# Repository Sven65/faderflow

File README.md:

# faderflow

> Fluid control over your desktop audio

A hardware audio mixer with motorized faders, full-color displays, and automatic application detection.

## Features

- 🎛️ 5 motorized faders with position sensing
- 🖥️ 5x 1.54" color TFT displays (240x240)
- 🔄 Bidirectional sync between hardware and Windows
- 🎯 Automatic app detection
- 📄 Multi-page navigation
- 💾 SD card icon storage

## Hardware

- Arduino Mega 2560
- 5x Behringer X32 Motorized Faders
- 3x DRV8833 Motor Driver Boards
- 6x ST7789 TFT Displays (1.54", 240x240)
- 6x EC11 Rotary Encoders
- SD Card Module
- USB-C PD Power (5V 3A)

## Software Stack

- **Desktop:** Rust + iced
- **Firmware:** Arduino C++
- **Platform:** Windows (Linux planned)

## Quick Start
```bash
# Clone repo
git clone https://github.com/Sven65/faderflow.git

# Build desktop app
cd desktop
cargo build --release

# Flash firmware
# Open firmware/faderflow/faderflow.ino in Arduino IDE
```

## Status

🚧 **Work in Progress** - Hardware picked out, software in development

## License

MIT License - see [LICENSE](LICENSE)

## Acknowledgments

Inspired by [deej](https://github.com/omriharel/deej)

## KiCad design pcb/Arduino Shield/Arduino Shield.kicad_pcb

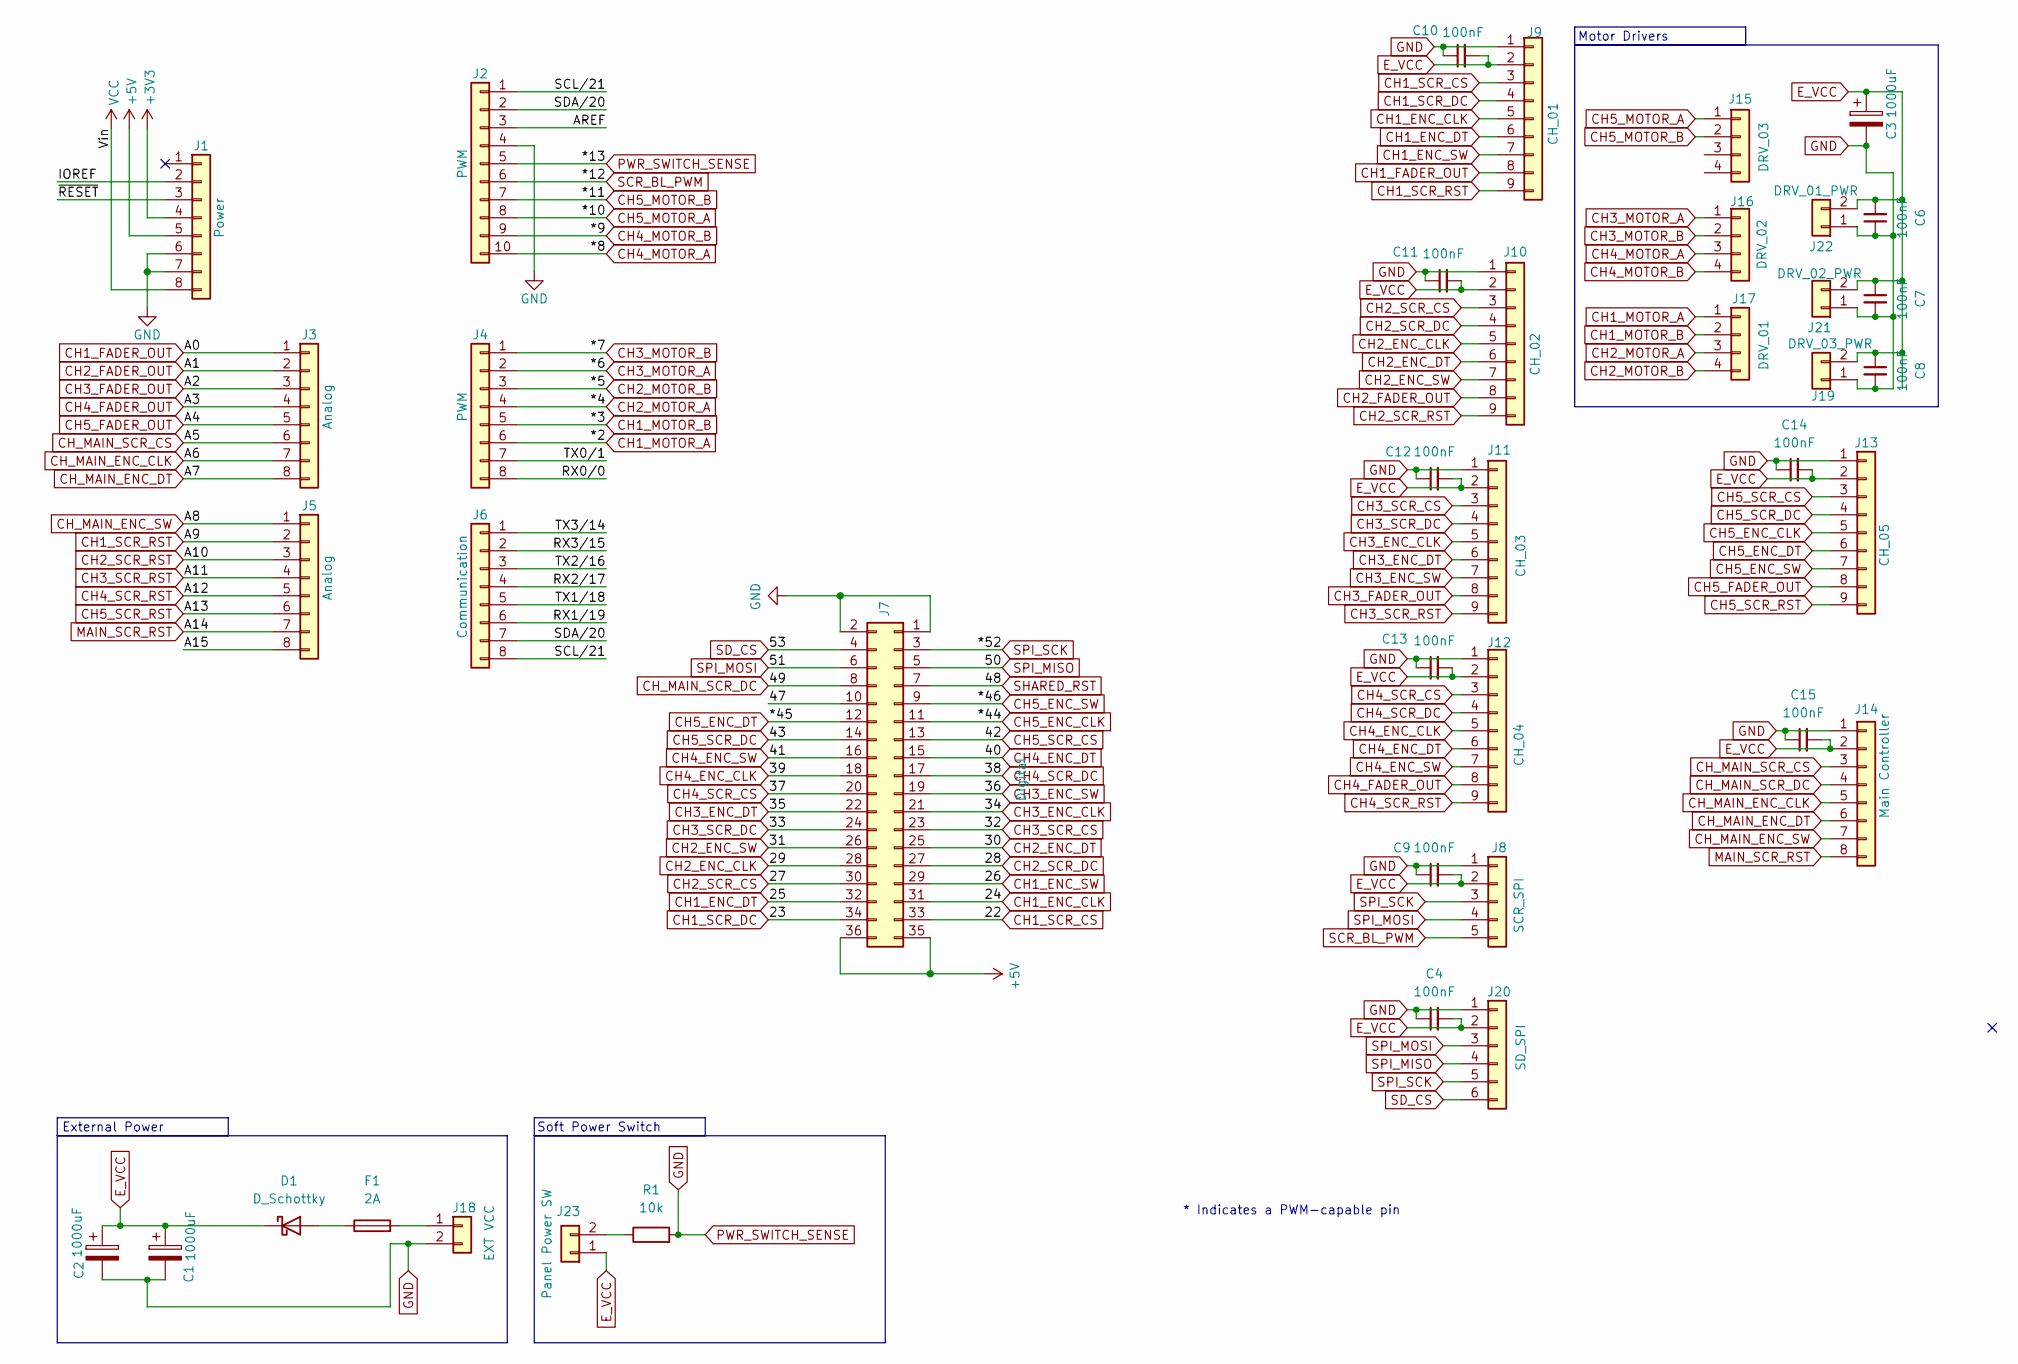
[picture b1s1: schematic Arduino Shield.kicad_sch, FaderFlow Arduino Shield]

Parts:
C1, C2, C3: 1000uF; CP_Radial_D8.0mm_P3.50mm
C4, C6, C7, C8, C9, C10, C11, C12, C13, C14, C15: 100nF; C_Disc_D5.0mm_W2.5mm_P5.00mm
D1: D_Schottky; D_DO-201AD_P15.24mm_Horizontal
F1: 2A; Fuseholder_Clip-5x20mm_Eaton_1A5601-01_Inline_P20.80x6.76mm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
J1: Power; PinSocket_1x08_P2.54mm_Vertical
J2: PWM; PinSocket_1x10_P2.54mm_Vertical
J3, J5: Analog; PinSocket_1x08_P2.54mm_Vertical
J4: PWM; PinSocket_1x08_P2.54mm_Vertical
J6: Communication; PinSocket_1x08_P2.54mm_Vertical
J7: Digital; PinSocket_2x18_P2.54mm_Vertical
J8: SCR_SPI; PinSocket_1x05_P2.00mm_Vertical
J9: CH_01; PinSocket_1x09_P2.00mm_Vertical
J10: CH_02; PinSocket_1x09_P2.00mm_Vertical
J11: CH_03; PinSocket_1x09_P2.00mm_Vertical
J12: CH_04; PinSocket_1x09_P2.00mm_Vertical
J13: CH_05; PinSocket_1x09_P2.00mm_Vertical
J14: Main Controller; PinSocket_1x08_P2.00mm_Vertical
J15: DRV_03; PinSocket_1x04_P2.00mm_Vertical
J16: DRV_02; PinSocket_1x04_P2.00mm_Vertical
J17: DRV_01; PinSocket_1x04_P2.00mm_Vertical
J18: EXT VCC; PinSocket_1x02_P2.00mm_Vertical
J19: DRV_03_PWR; PinSocket_1x02_P2.00mm_Vertical
J20: SD_SPI; PinSocket_1x06_P2.00mm_Vertical
J21: DRV_02_PWR; PinSocket_1x02_P2.00mm_Vertical
J22: DRV_01_PWR; PinSocket_1x02_P2.00mm_Vertical
J23: Panel Power SW; PinSocket_1x02_P2.00mm_Vertical
R1: 10k; R_Axial_DIN0207_L6.3mm_D2.5mm_P10.16mm_Horizontal

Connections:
+3V3: J1.4
+5V: J1.5, J7.35, J7.36
/47: J7.10
/A15: J5.8
/AREF: J2.3
/IOREF: J1.2
/RX0/0: J4.8
/RX1/19: J6.6
/RX2/17: J6.4
/RX3/15: J6.2
/SCL/21: J2.1, J6.8
/SDA/20: J2.2, J6.7
/TX0/1: J4.7
/TX1/18: J6.5
/TX2/16: J6.3
/TX3/14: J6.1
/~RESET: J1.3
CH1_ENC_CLK: J7.31, J9.5
CH1_ENC_DT: J7.32, J9.6
CH1_ENC_SW: J7.29, J9.7
CH1_FADER_OUT: J3.1, J9.8
CH1_MOTOR_A: J4.6, J17.1
CH1_MOTOR_B: J4.5, J17.2
CH1_SCR_CS: J7.33, J9.3
CH1_SCR_DC: J7.34, J9.4
CH1_SCR_RST: J5.2, J9.9
CH2_ENC_CLK: J7.28, J10.5
CH2_ENC_DT: J7.25, J10.6
CH2_ENC_SW: J7.26, J10.7
CH2_FADER_OUT: J3.2, J10.8
CH2_MOTOR_A: J4.4, J17.3
CH2_MOTOR_B: J4.3, J17.4
CH2_SCR_CS: J7.30, J10.3
CH2_SCR_DC: J7.27, J10.4
CH2_SCR_RST: J5.3, J10.9
CH3_ENC_CLK: J7.21, J11.5
CH3_ENC_DT: J7.22, J11.6
CH3_ENC_SW: J7.19, J11.7
CH3_FADER_OUT: J3.3, J11.8
CH3_MOTOR_A: J4.2, J16.1
CH3_MOTOR_B: J4.1, J16.2
CH3_SCR_CS: J7.23, J11.3
CH3_SCR_DC: J7.24, J11.4
CH3_SCR_RST: J5.4, J11.9
CH4_ENC_CLK: J7.18, J12.5
CH4_ENC_DT: J7.15, J12.6
CH4_ENC_SW: J7.16, J12.7
CH4_FADER_OUT: J3.4, J12.8
CH4_MOTOR_A: J2.10, J16.3
CH4_MOTOR_B: J2.9, J16.4
CH4_SCR_CS: J7.20, J12.3
CH4_SCR_DC: J7.17, J12.4
CH4_SCR_RST: J5.5, J12.9
CH5_ENC_CLK: J7.11, J13.5
CH5_ENC_DT: J7.12, J13.6
CH5_ENC_SW: J7.9, J13.7
CH5_FADER_OUT: J3.5, J13.8
CH5_MOTOR_A: J2.8, J15.1
CH5_MOTOR_B: J2.7, J15.2
CH5_SCR_CS: J7.13, J13.3
CH5_SCR_DC: J7.14, J13.4
CH5_SCR_RST: J5.6, J13.9
CH_MAIN_ENC_CLK: J3.7, J14.5
CH_MAIN_ENC_DT: J3.8, J14.6
CH_MAIN_ENC_SW: J5.1, J14.7
CH_MAIN_SCR_CS: J3.6, J14.3
CH_MAIN_SCR_DC: J7.8, J14.4
E_VCC: C1.1, C2.1, C3.1, C4.2, C6.2, C7.1, C8.1, C9.2, C10.2, C11.2, C12.2, C13.2, C14.2, C15.2, D1.1 (K), J8.2, J9.2, J10.2, J11.2, J12.2, J13.2, J14.2, J19.2, J20.2, J21.2, J22.2, J23.1
GND: C1.2, C2.2, C3.2, C4.1, C6.1, C7.2, C8.2, C9.1, C10.1, C11.1, C12.1, C13.1, C14.1, C15.1, J1.6, J1.7, J2.4, J2.5, J7.1, J7.2, J8.1, J9.1, J10.1, J11.1, J12.1, J13.1, J14.1, J18.2, J19.1, J20.1, J21.1, J22.1, R1.2
MAIN_SCR_RST: J5.7, J14.8
unnamed: D1.2 (A), F1.1
unnamed: F1.2, J18.1
unnamed: J23.2, R1.1
SCR_BL_PWM: J2.6, J8.5
SD_CS: J7.4, J20.6
SHARED_RST: J7.7
SPI_MISO: J7.5, J20.4
SPI_MOSI: J7.6, J8.4, J20.3
SPI_SCK: J7.3, J8.3, J20.5
VCC: J1.8

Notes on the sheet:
External Power
Soft Power Switch
Motor Drivers
* Indicates a PWM-capable pin

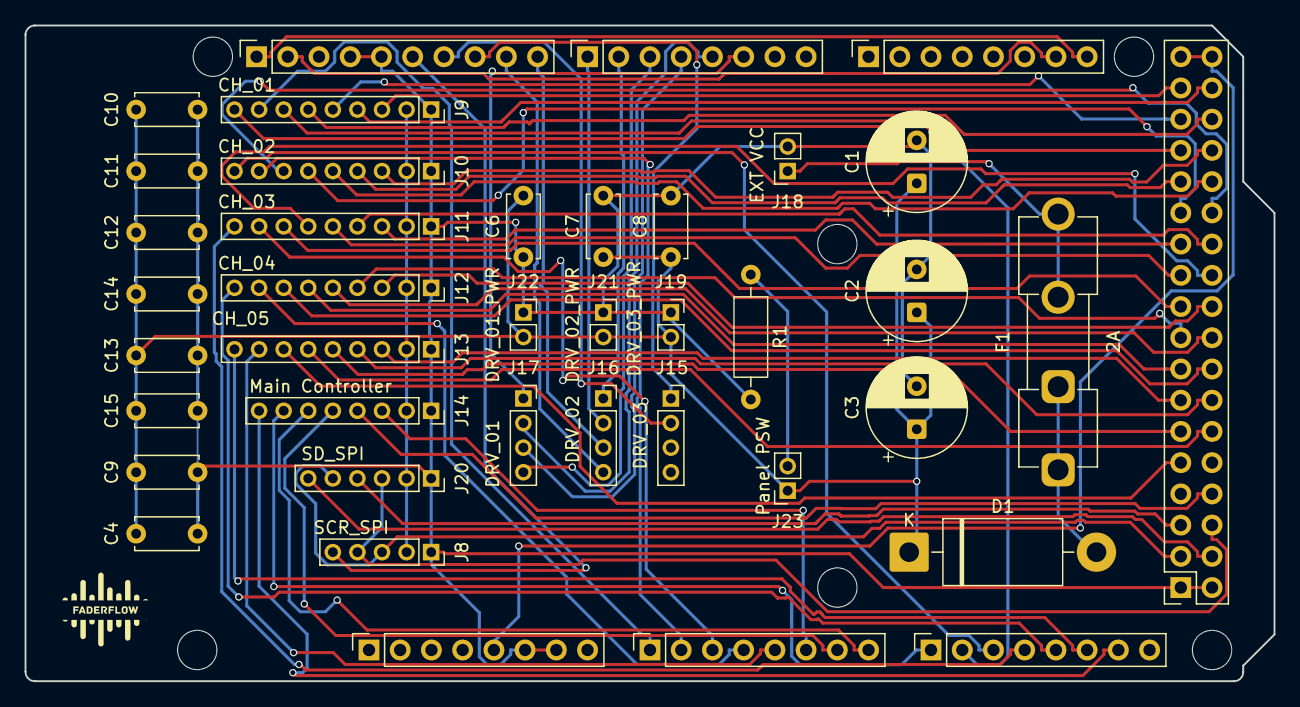
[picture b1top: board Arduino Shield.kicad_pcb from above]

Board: 2 copper layers, 101.6 x 53.3 mm, 46 parts (0 on the bottom side), 64 nets.

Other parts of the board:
MH1, MH2, MH3, MH4, MH5, MH6: MountingHole_3.2mm

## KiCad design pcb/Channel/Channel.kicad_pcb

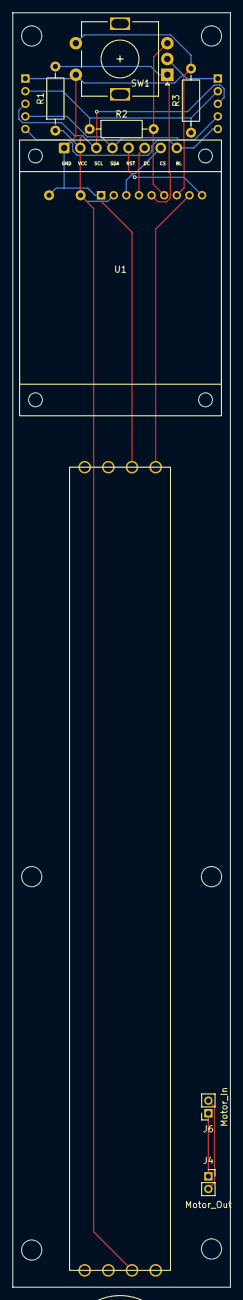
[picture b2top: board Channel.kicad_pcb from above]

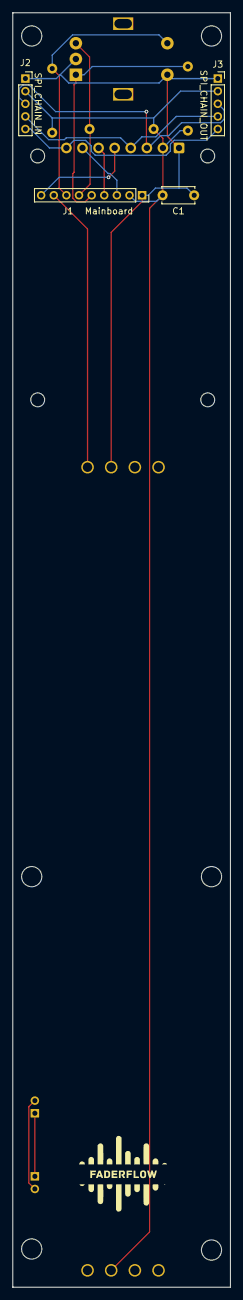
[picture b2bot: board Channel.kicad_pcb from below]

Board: 2 copper layers, 34.5 x 202.0 mm, 18 parts (4 on the bottom side), 14 nets.

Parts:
C1: 0.1uF; C_Disc_D5.0mm_W2.5mm_P5.00mm
F1: Behringer X32 Fader
J1: Mainboard; PinSocket_1x09_P2.00mm_Vertical
J2: SPI_CHAIN_IN; PinSocket_1x05_P2.00mm_Vertical
J3: SPI_CHAIN_OUT; PinSocket_1x05_P2.00mm_Vertical
J4: Motor_Out; PinSocket_1x02_P2.00mm_Vertical
J6: Motor_In; PinSocket_1x02_P2.00mm_Vertical
Mount_1, Mount_2, Mount_3, Mount_4, Mount_6, Mount_7: MountingHole_3.2mm_M3
R1, R2, R3: 10k; R_Axial_DIN0207_L6.3mm_D2.5mm_P10.16mm_Horizontal
SW1: RotaryEncoder_Switch; RotaryEncoder_Alps_EC11E-Switch_Vertical_H20mm
U1: 1.54 inch

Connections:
ENC_CLK: J1.5, R1.2, SW1.A
ENC_DT: J1.6, R2.2, SW1.B
ENC_SW: J1.7, R3.2, SW1.S1
E_VCC: C1.2, F1.3 (T2), J1.2, J2.2, J3.2, R1.1, R2.1, R3.1, U1.2 (VCC)
FADER_OUT: F1.2 (W), J1.8
GND: C1.1, F1.1 (T1), J1.1, J2.1, J3.1, SW1.C, SW1.S2, U1.1 (GND)
MOTOR+: J4.1, J6.1
MOTOR-: J4.2, J6.2
SCREEN_CS: J1.3, U1.7 (CS)
SCREEN_DC: J1.4, U1.6 (DC)
SCREEN_RST: J1.9, U1.5 (RST)
SCR_BL_PWM: J2.5, J3.5, U1.8 (BL)
SPI_MOSI: J2.4, J3.4, U1.4 (SDA)
SPI_SCK: J2.3, J3.3, U1.3 (SCL)

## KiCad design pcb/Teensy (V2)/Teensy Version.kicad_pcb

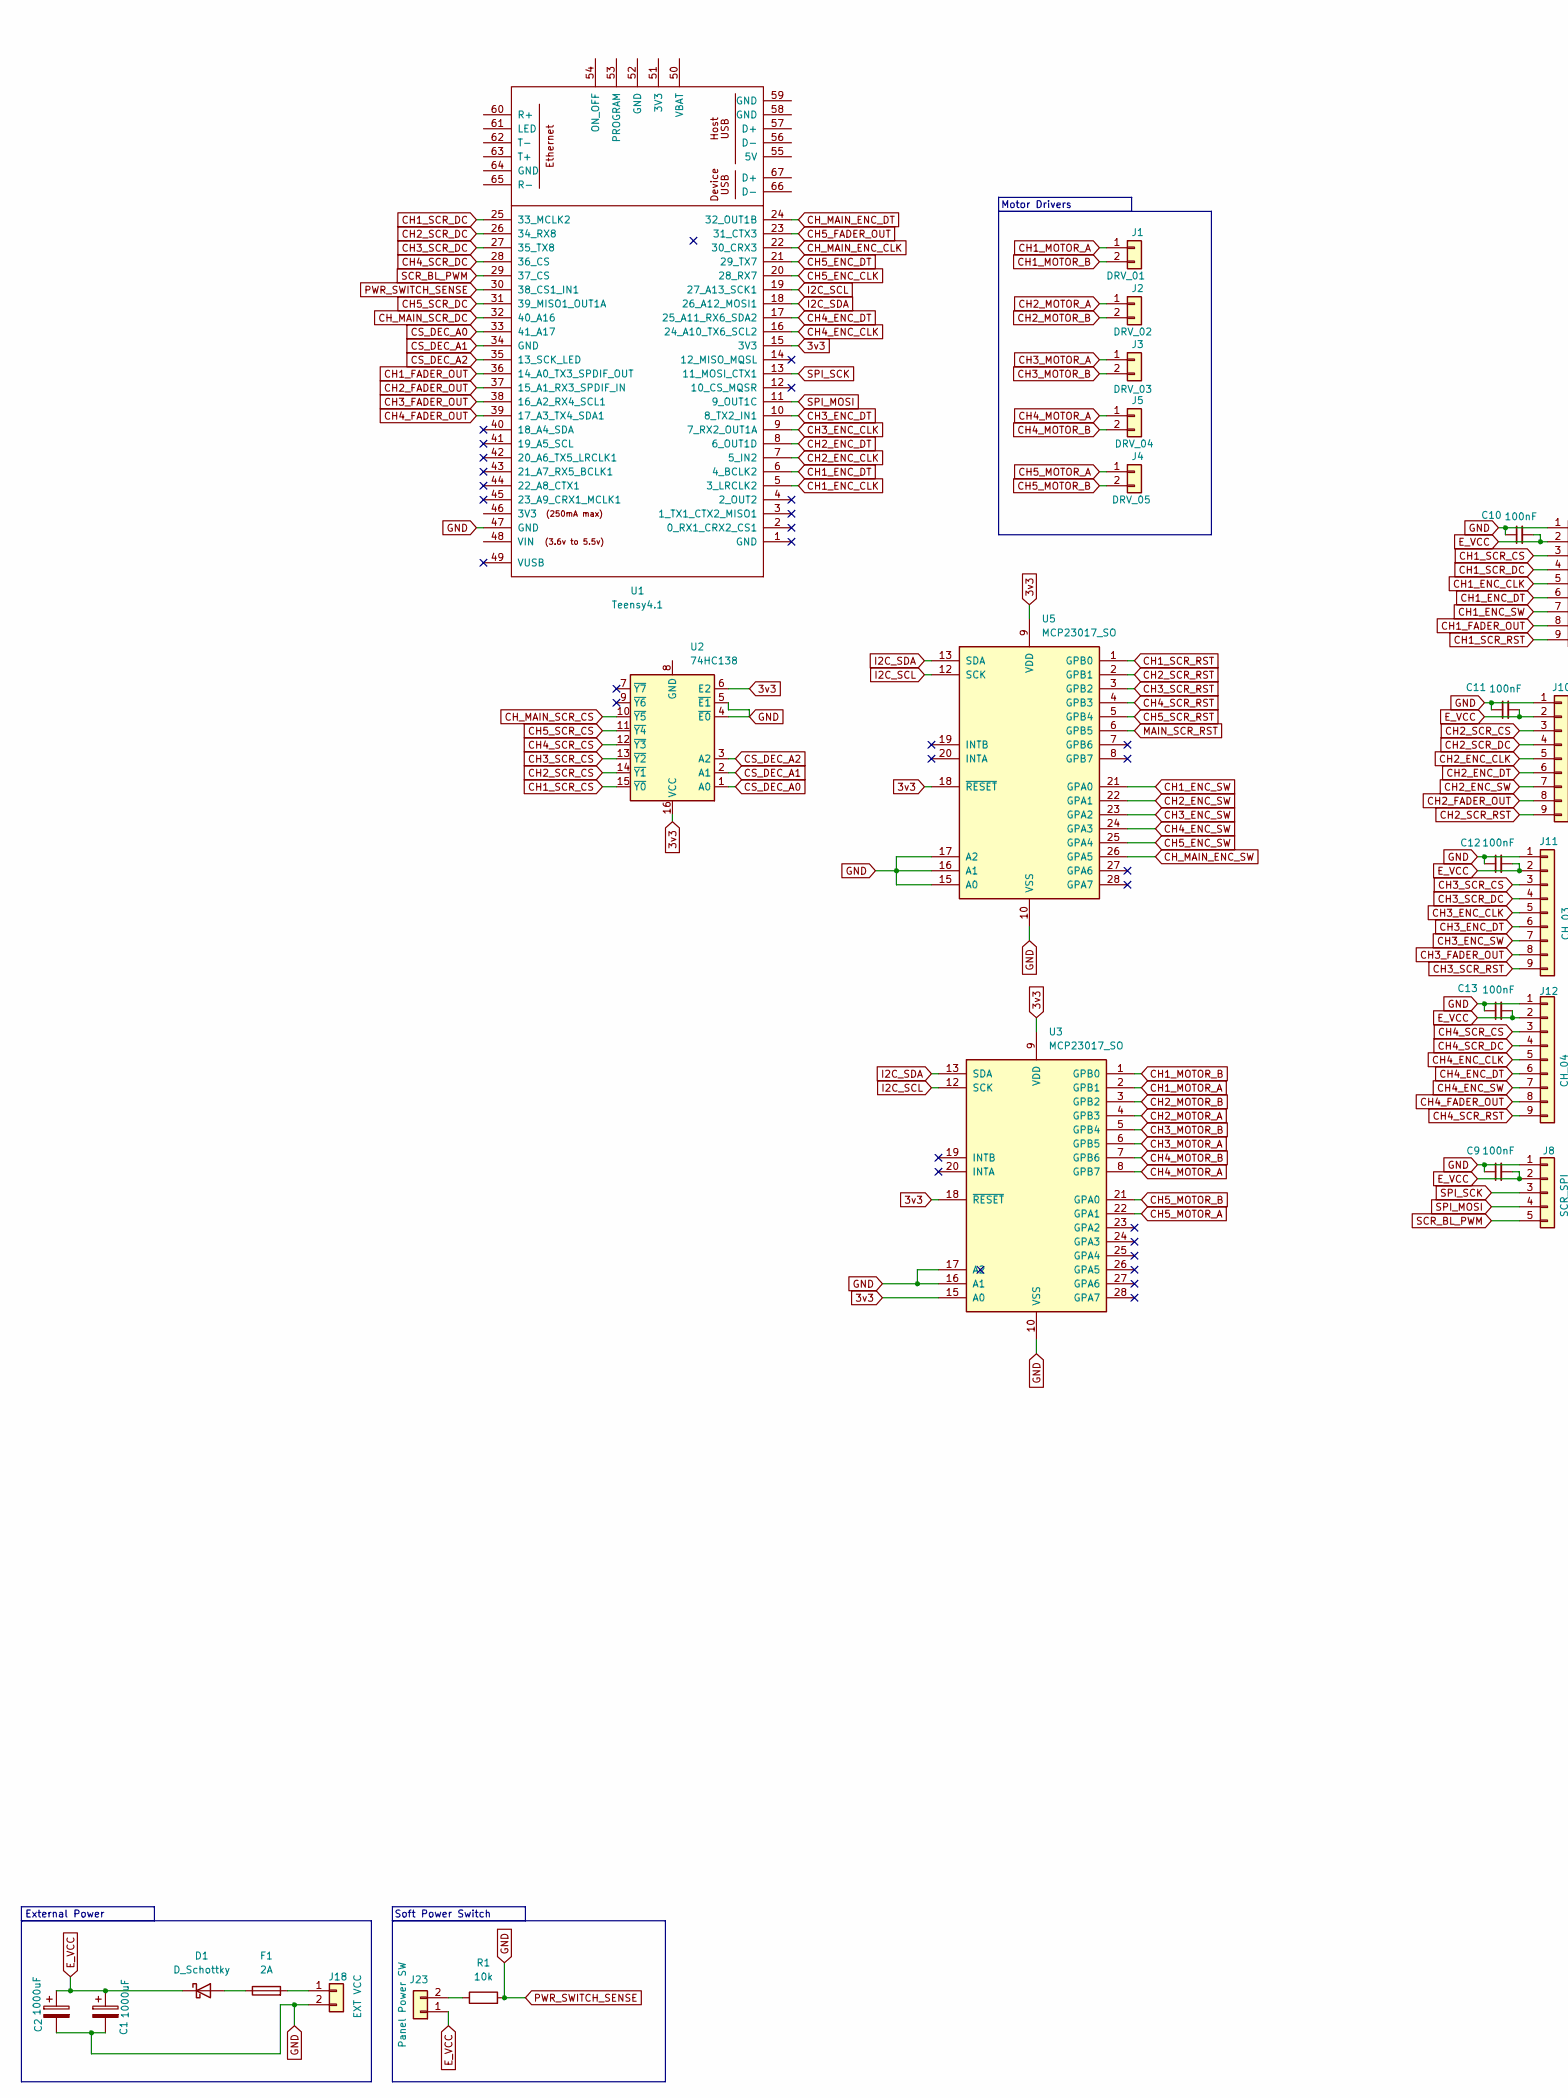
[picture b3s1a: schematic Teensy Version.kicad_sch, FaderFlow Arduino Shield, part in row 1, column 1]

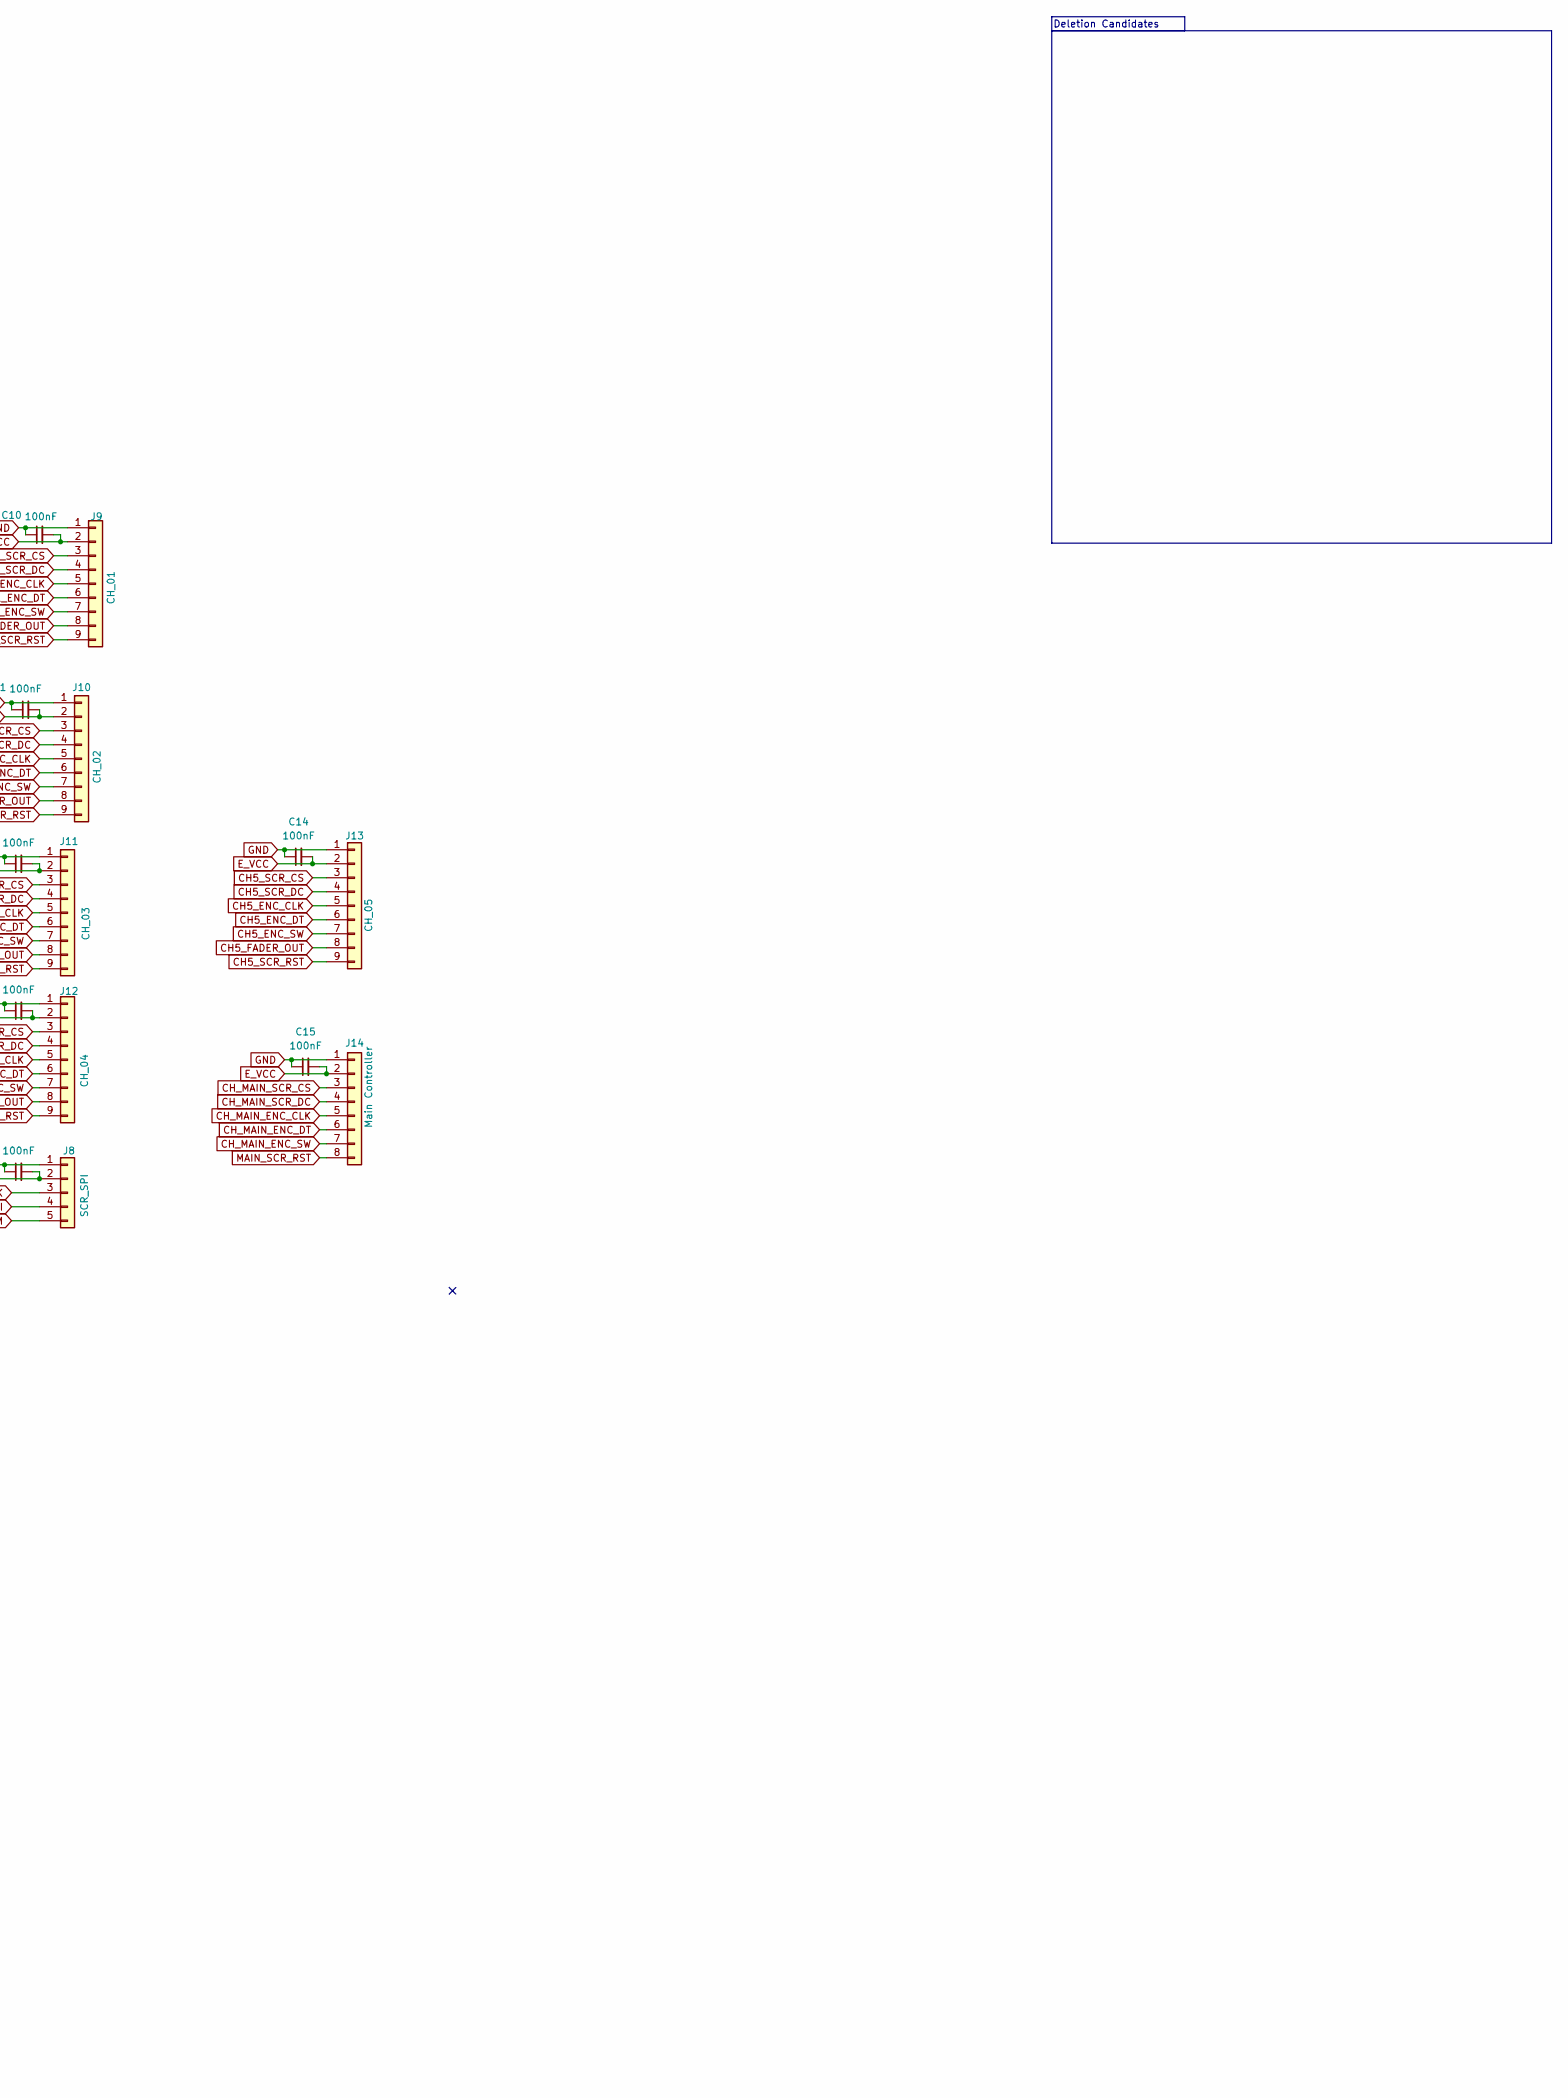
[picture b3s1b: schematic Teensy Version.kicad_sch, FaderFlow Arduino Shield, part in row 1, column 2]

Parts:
C1, C2: 1000uF; CP_Radial_D8.0mm_P3.50mm
C9, C10, C11, C12, C13, C14, C15: 100nF; C_Disc_D5.0mm_W2.5mm_P5.00mm
D1: D_Schottky; D_DO-201AD_P15.24mm_Horizontal
F1: 2A; Fuseholder_Clip-5x20mm_Eaton_1A5601-01_Inline_P20.80x6.76mm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
J1: DRV_01; PinSocket_1x02_P2.00mm_Vertical
J2: DRV_02; PinSocket_1x02_P2.00mm_Vertical
J3: DRV_03; PinSocket_1x02_P2.00mm_Vertical
J4: DRV_05; PinSocket_1x02_P2.00mm_Vertical
J5: DRV_04; PinSocket_1x02_P2.00mm_Vertical
J8: SCR_SPI; PinSocket_1x05_P2.00mm_Vertical
J9: CH_01; PinSocket_1x09_P2.00mm_Vertical
J10: CH_02; PinSocket_1x09_P2.00mm_Vertical
J11: CH_03; PinSocket_1x09_P2.00mm_Vertical
J12: CH_04; PinSocket_1x09_P2.00mm_Vertical
J13: CH_05; PinSocket_1x09_P2.00mm_Vertical
J14: Main Controller; PinSocket_1x08_P2.00mm_Vertical
J18: EXT VCC; PinSocket_1x02_P2.00mm_Vertical
J23: Panel Power SW; PinSocket_1x02_P2.00mm_Vertical
R1: 10k; R_Axial_DIN0207_L6.3mm_D2.5mm_P10.16mm_Horizontal
U1: Teensy4.1; Teensy41
U2: 74HC138; SO-16_3.9x9.9mm_P1.27mm
U3, U5: MCP23017_SO; SOIC-28W_7.5x17.9mm_P1.27mm

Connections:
3v3: U1.15 (3V3), U2.6 (E2), U2.16 (VCC), U3.9 (VDD), U3.15 (A0), U3.18 (~RESET), U5.9 (VDD), U5.18 (~RESET)
CH1_ENC_CLK: J9.5, U1.5 (3_LRCLK2)
CH1_ENC_DT: J9.6, U1.6 (4_BCLK2)
CH1_ENC_SW: J9.7, U5.21 (GPA0)
CH1_FADER_OUT: J9.8, U1.36 (14_A0_TX3_SPDIF_OUT)
CH1_MOTOR_A: J1.1, U3.2 (GPB1)
CH1_MOTOR_B: J1.2, U3.1 (GPB0)
CH1_SCR_CS: J9.3, U2.15 (~Y0)
CH1_SCR_DC: J9.4, U1.25 (33_MCLK2)
CH1_SCR_RST: J9.9, U5.1 (GPB0)
CH2_ENC_CLK: J10.5, U1.7 (5_IN2)
CH2_ENC_DT: J10.6, U1.8 (6_OUT1D)
CH2_ENC_SW: J10.7, U5.22 (GPA1)
CH2_FADER_OUT: J10.8, U1.37 (15_A1_RX3_SPDIF_IN)
CH2_MOTOR_A: J2.1, U3.4 (GPB3)
CH2_MOTOR_B: J2.2, U3.3 (GPB2)
CH2_SCR_CS: J10.3, U2.14 (~Y1)
CH2_SCR_DC: J10.4, U1.26 (34_RX8)
CH2_SCR_RST: J10.9, U5.2 (GPB1)
CH3_ENC_CLK: J11.5, U1.9 (7_RX2_OUT1A)
CH3_ENC_DT: J11.6, U1.10 (8_TX2_IN1)
CH3_ENC_SW: J11.7, U5.23 (GPA2)
CH3_FADER_OUT: J11.8, U1.38 (16_A2_RX4_SCL1)
CH3_MOTOR_A: J3.1, U3.6 (GPB5)
CH3_MOTOR_B: J3.2, U3.5 (GPB4)
CH3_SCR_CS: J11.3, U2.13 (~Y2)
CH3_SCR_DC: J11.4, U1.27 (35_TX8)
CH3_SCR_RST: J11.9, U5.3 (GPB2)
CH4_ENC_CLK: J12.5, U1.16 (24_A10_TX6_SCL2)
CH4_ENC_DT: J12.6, U1.17 (25_A11_RX6_SDA2)
CH4_ENC_SW: J12.7, U5.24 (GPA3)
CH4_FADER_OUT: J12.8, U1.39 (17_A3_TX4_SDA1)
CH4_MOTOR_A: J5.1, U3.8 (GPB7)
CH4_MOTOR_B: J5.2, U3.7 (GPB6)
CH4_SCR_CS: J12.3, U2.12 (~Y3)
CH4_SCR_DC: J12.4, U1.28 (36_CS)
CH4_SCR_RST: J12.9, U5.4 (GPB3)
CH5_ENC_CLK: J13.5, U1.20 (28_RX7)
CH5_ENC_DT: J13.6, U1.21 (29_TX7)
CH5_ENC_SW: J13.7, U5.25 (GPA4)
CH5_FADER_OUT: J13.8, U1.23 (31_CTX3)
CH5_MOTOR_A: J4.1, U3.22 (GPA1)
CH5_MOTOR_B: J4.2, U3.21 (GPA0)
CH5_SCR_CS: J13.3, U2.11 (~Y4)
CH5_SCR_DC: J13.4, U1.31 (39_MISO1_OUT1A)
CH5_SCR_RST: J13.9, U5.5 (GPB4)
CH_MAIN_ENC_CLK: J14.5, U1.22 (30_CRX3)
CH_MAIN_ENC_DT: J14.6, U1.24 (32_OUT1B)
CH_MAIN_ENC_SW: J14.7, U5.26 (GPA5)
CH_MAIN_SCR_CS: J14.3, U2.10 (~Y5)
CH_MAIN_SCR_DC: J14.4, U1.32 (40_A16)
CS_DEC_A0: U1.33 (41_A17), U2.1 (A0)
CS_DEC_A1: U1.34 (GND), U2.2 (A1)
CS_DEC_A2: U1.35 (13_SCK_LED), U2.3 (A2)
E_VCC: C1.1, C2.1, C9.2, C10.2, C11.2, C12.2, C13.2, C14.2, C15.2, D1.1 (K), J8.2, J9.2, J10.2, J11.2, J12.2, J13.2, J14.2, J23.1
GND: C1.2, C2.2, C9.1, C10.1, C11.1, C12.1, C13.1, C14.1, C15.1, J8.1, J9.1, J10.1, J11.1, J12.1, J13.1, J14.1, J18.2, R1.2, U1.30 (38_CS1_IN1), U1.47 (GND), U2.4 (~E0), U2.5 (~E1), U3.10 (VSS), U3.16 (A1), U3.17 (A2), U5.10 (VSS), U5.15 (A0), U5.16 (A1), U5.17 (A2)
I2C_SCL: U1.19 (27_A13_SCK1), U3.12 (SCK), U5.12 (SCK)
I2C_SDA: U1.18 (26_A12_MOSI1), U3.13 (SDA), U5.13 (SDA)
MAIN_SCR_RST: J14.8, U5.6 (GPB5)
unnamed: D1.2 (A), F1.1
unnamed: F1.2, J18.1
unnamed: J23.2, R1.1
SCR_BL_PWM: J8.5, U1.29 (37_CS)
SPI_MOSI: J8.4, U1.11 (9_OUT1C)
SPI_SCK: J8.3, U1.13 (11_MOSI_CTX1)

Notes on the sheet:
External Power
Deletion Candidates
Soft Power Switch
Motor Drivers

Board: 2 copper layers, 30 parts (0 on the bottom side), 65 nets, no tracks yet.

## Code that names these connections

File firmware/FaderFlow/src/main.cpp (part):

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const int8_t  CS_PINS[NUM_CHANNELS]   = { 22, 27, 32, 37, 42 };
const int8_t  DC_PINS[NUM_CHANNELS]   = { 23, 28, 33, 38, 43 };
const int8_t  RST_PINS[NUM_CHANNELS]  = { 63, 64, 65, 66, 67 };  // A9-A13
const uint8_t ENC_CLK[NUM_CHANNELS]   = { 24, 29, 34, 39, 44 };
const uint8_t ENC_DT[NUM_CHANNELS]    = { 25, 30, 35, 40, 45 };
const uint8_t ENC_SW[NUM_CHANNELS]    = { 26, 31, 36, 41, 46 };
const uint8_t MOTOR_A[NUM_CHANNELS]   = { 2, 4, 6, 8, 10 };      // all PWM
const uint8_t MOTOR_B[NUM_CHANNELS]   = { 3, 5, 7, 9, 11 };
const uint8_t FADER_PIN[NUM_CHANNELS] = { A0, A1, A2, A3, A4 };
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
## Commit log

2026-02-04 Basic volume sync
2026-02-04 Fix gui in readme
2026-02-04 Add icons
2026-02-07 Restructure project, add mute button
2026-02-07 Add todo
2026-02-11 Start working on firmware for hardware
2026-02-11 Add Initial arduino shield file
2026-02-12 Update shield pcb silkscreen
2026-02-12 Update pcb, start channel
2026-02-13 Update main PCB to use 9pin connectors for channels (They need unique RST)
2026-02-13 Fix gitignore, start icons and channel pcbs
2026-02-13 Make arduino code more structured, start appname and volume sync protocols.
2026-02-13 Improve handshaking.
2026-02-16 Update main pcb silkscreen.
2026-02-16 Update the gerbers
2026-02-16 Add drills and edge cut gerbers.
2026-02-16 Silkscreen updates.
2026-02-16 Update UI
2026-02-18 Start a potential V2 mainboard with teensy
2026-02-21 Fix up channel pcb
2026-02-21 Update pcb gerbers,
2026-02-21 Move views into their own files
2026-02-23 Update pcb gerbers
2026-02-23 Update firmware and desktop app
2026-02-23 Update UI and device handling.
2026-06-12 Get firmware and sofware working better with hardware, in terms of all 5 channels and motorized faders.
2026-06-12 Update icon code, change packet handling
2026-06-12 Start calib stuff
2026-06-13 Improve calibration
